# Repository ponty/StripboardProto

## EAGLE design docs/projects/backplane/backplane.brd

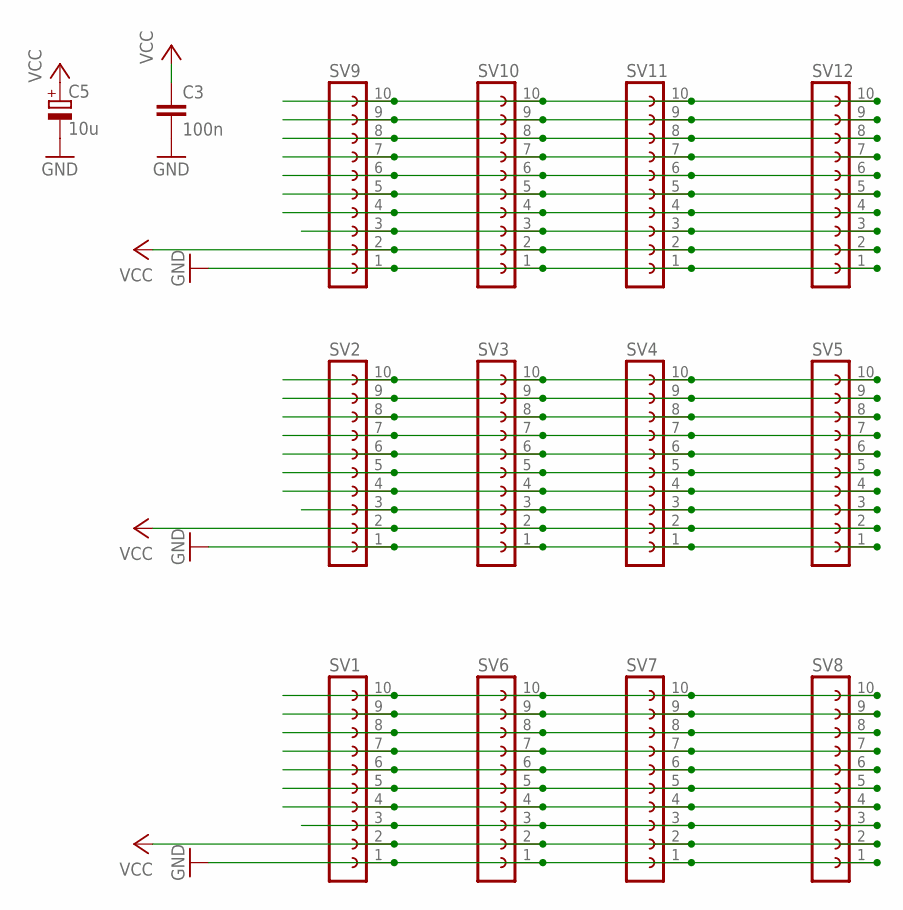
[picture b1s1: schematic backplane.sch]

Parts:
C3: 100n; C025-024X044
C5: 10u; E2,5-6E
SV1, SV2, SV3, SV4, SV5, SV6, SV7, SV8, SV9, SV10, SV11, SV12: FE10-1; FE10

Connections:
GND: C3.2, C5.-, SV1.1, SV2.1, SV3.1, SV4.1, SV5.1, SV6.1, SV7.1, SV8.1, SV9.1, SV10.1, SV11.1, SV12.1
unnamed: SV2.4, SV3.4, SV4.4, SV5.4
unnamed: SV2.10, SV3.10, SV4.10, SV5.10
unnamed: SV2.3, SV3.3, SV4.3, SV5.3
unnamed: SV2.9, SV3.9, SV4.9, SV5.9
unnamed: SV2.8, SV3.8, SV4.8, SV5.8
unnamed: SV2.7, SV3.7, SV4.7, SV5.7
unnamed: SV2.6, SV3.6, SV4.6, SV5.6
unnamed: SV2.5, SV3.5, SV4.5, SV5.5
unnamed: SV1.10, SV6.10, SV7.10, SV8.10
unnamed: SV1.9, SV6.9, SV7.9, SV8.9
unnamed: SV1.8, SV6.8, SV7.8, SV8.8
unnamed: SV1.7, SV6.7, SV7.7, SV8.7
unnamed: SV1.6, SV6.6, SV7.6, SV8.6
unnamed: SV1.5, SV6.5, SV7.5, SV8.5
unnamed: SV1.4, SV6.4, SV7.4, SV8.4
unnamed: SV1.3, SV6.3, SV7.3, SV8.3
unnamed: SV9.10, SV10.10, SV11.10, SV12.10
unnamed: SV9.9, SV10.9, SV11.9, SV12.9
unnamed: SV9.8, SV10.8, SV11.8, SV12.8
unnamed: SV9.7, SV10.7, SV11.7, SV12.7
unnamed: SV9.6, SV10.6, SV11.6, SV12.6
unnamed: SV9.5, SV10.5, SV11.5, SV12.5
unnamed: SV9.4, SV10.4, SV11.4, SV12.4
unnamed: SV9.3, SV10.3, SV11.3, SV12.3
VCC: C3.1, C5.+, SV1.2, SV2.2, SV3.2, SV4.2, SV5.2, SV6.2, SV7.2, SV8.2, SV9.2, SV10.2, SV11.2, SV12.2

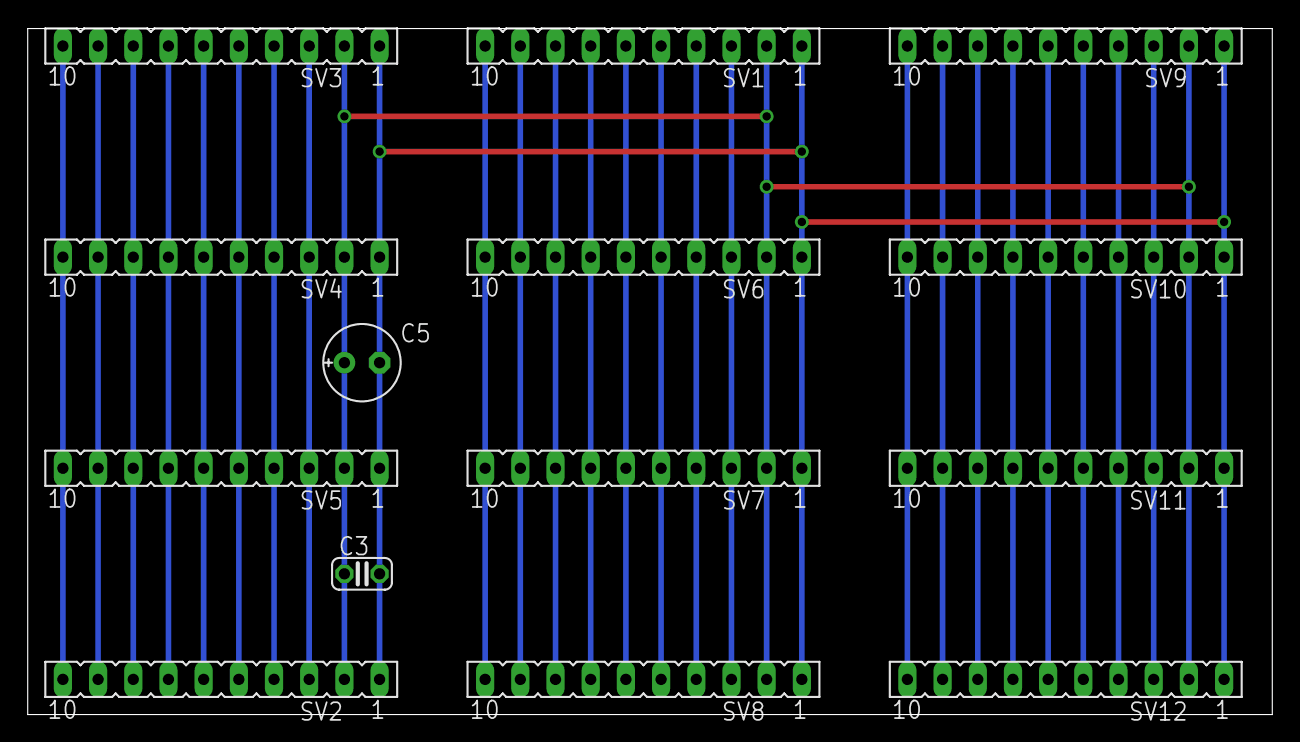
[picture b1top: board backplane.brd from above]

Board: 2 copper layers, 89.8 x 49.5 mm, 14 parts (0 on the bottom side), 26 nets.

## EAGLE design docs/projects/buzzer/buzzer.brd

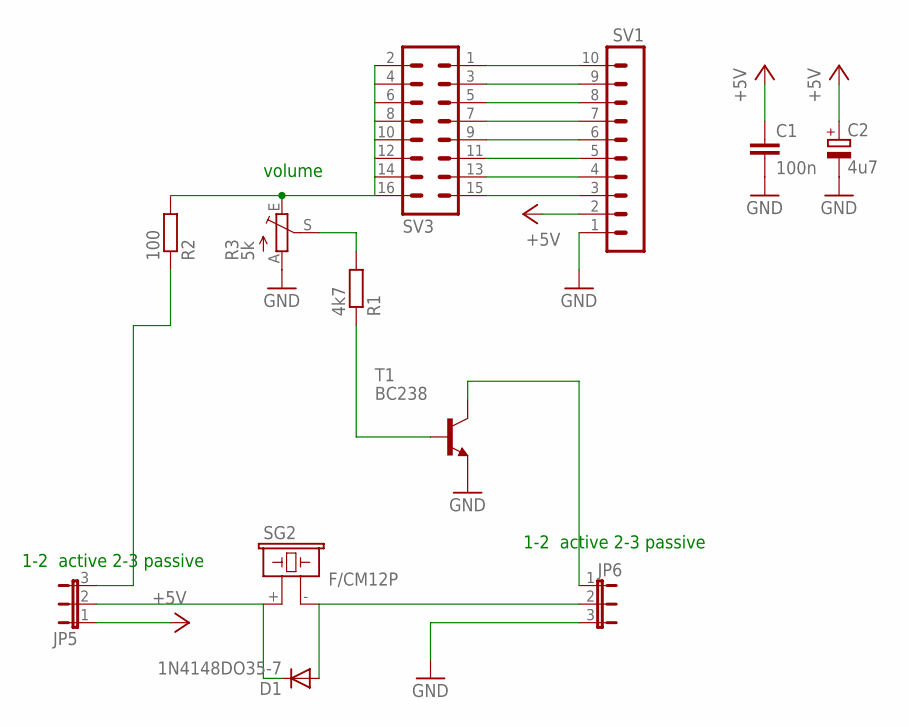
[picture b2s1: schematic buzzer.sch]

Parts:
C1: 100n; C025-024X044
C2: 4u7; TT2D5
D1: 1N4148DO35-7; DO35-7
JP5, JP6: JP2W
R1: 4k7; 0617/17
R2: 100; 0207/10
R3: 5k; CA9V
SG2: F/CM12P
SV1: MA10-1W
SV3: MA08-2
T1: BC238; TO5

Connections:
+5V: C1.1, C2.+, JP5.1, SV1.2
GND: C1.2, C2.-, JP6.3, R3.A, SV1.1, T1.1 (E)
unnamed: R2.2, R3.E, SV3.2, SV3.4, SV3.6, SV3.8, SV3.10, SV3.12, SV3.14, SV3.16
unnamed: R1.2, R3.S
unnamed: R1.1, T1.2 (B)
unnamed: D1.C, JP5.2, SG2.+ (1)
unnamed: JP5.3, R2.1
unnamed: SV1.3, SV3.15
unnamed: D1.A, JP6.2, SG2.- (2)
unnamed: SV1.4, SV3.13
unnamed: SV1.5, SV3.11
unnamed: JP6.1, T1.3 (C)
unnamed: SV1.6, SV3.9
unnamed: SV1.7, SV3.7
unnamed: SV1.8, SV3.5
unnamed: SV1.9, SV3.3
unnamed: SV1.10, SV3.1

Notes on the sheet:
1-2 active 2-3 passive
volume

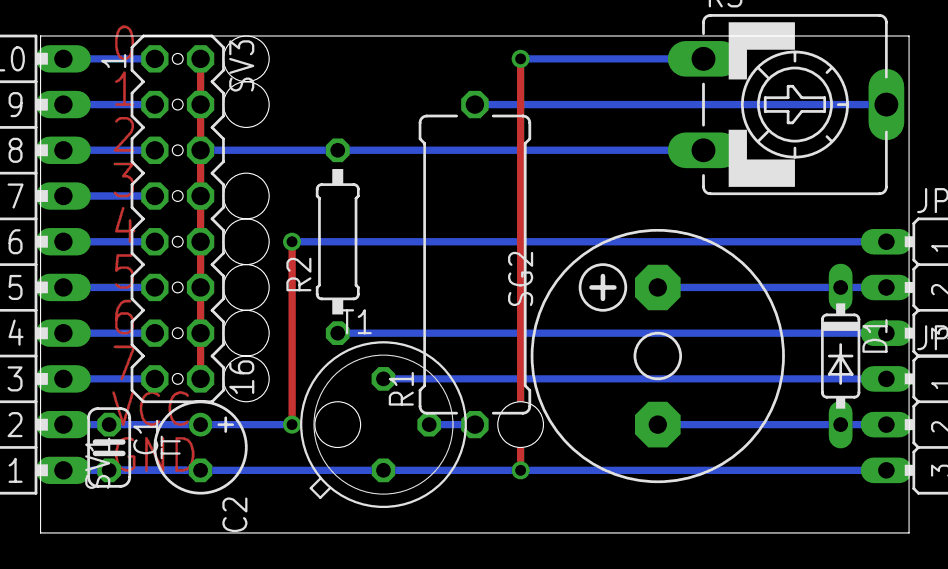
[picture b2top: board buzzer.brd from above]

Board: 2 copper layers, 48.2 x 27.6 mm, 12 parts (0 on the bottom side), 17 nets.

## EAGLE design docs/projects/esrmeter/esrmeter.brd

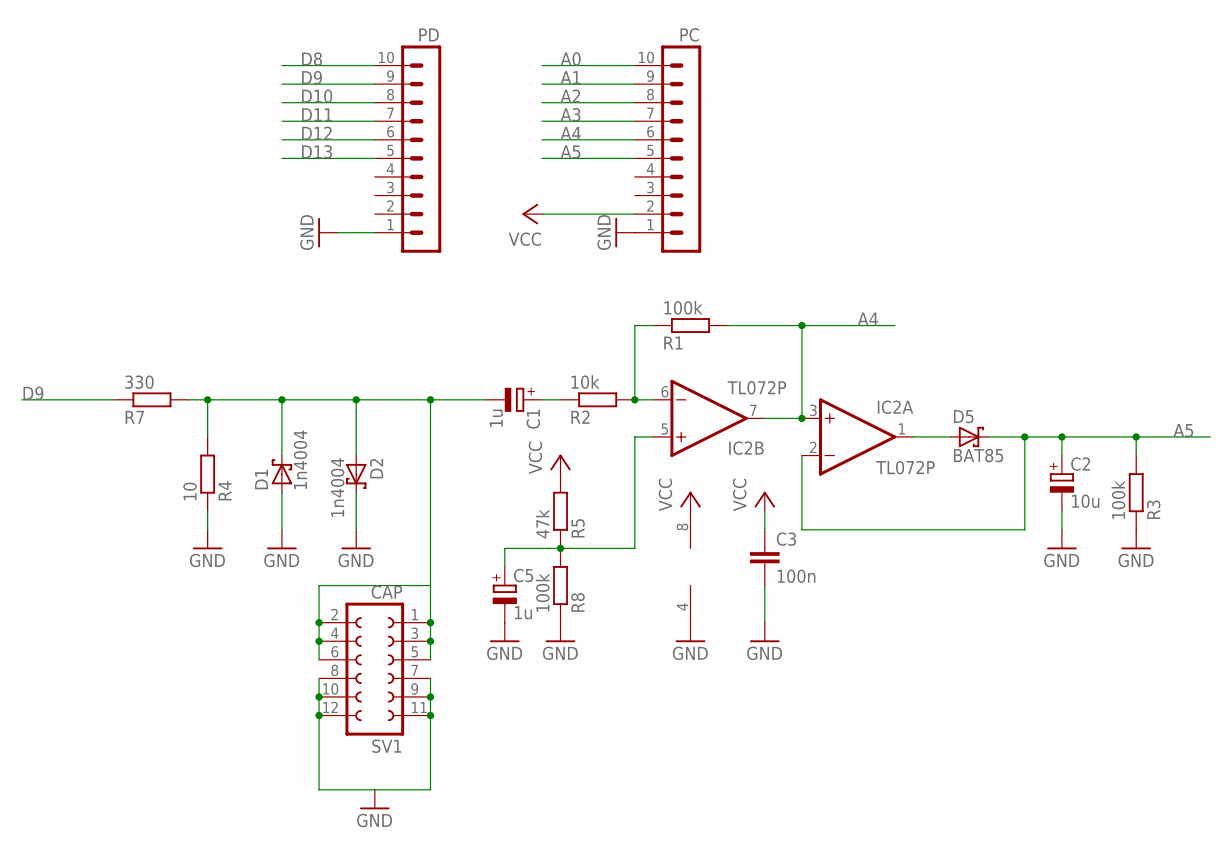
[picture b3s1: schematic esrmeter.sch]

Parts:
C1: 1u; TT2D6
C2: 10u; TT5D7
C3: 100n; C025-024X044
C5: 1u; TT5D7
D1, D2: 1n4004; TO92H
D5: BAT85; TO92H
IC2: TL072P; DIL08
PC: MA10-1W
PD: MA10-1W
R1: 100k; 0207/2V
R2: 10k; 0617/17
R3: 100k; 0207/10
R4: 10; 0207/2V
R5: 47k; 0207/2V
R7: 330; 0617/22
R8: 100k; 0204/5
SV1: CAP; FE06-2W

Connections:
A0: PC.10
A1: PC.9
A2: PC.8
A3: PC.7
A4: IC2.3 (+IN), IC2.7 (OUT), PC.6, R1.2
A5: C2.+, D5.2 (C), IC2.2 (-IN), PC.5, R3.2
D8: PD.10
D9: PD.9, R7.1
D10: PD.8
D11: PD.7
D12: PD.6
D13: PD.5
GND: C2.-, C3.2, C5.-, D1.1 (A), D2.2 (C), IC2.4 (V-), PC.1, PD.1, R3.1, R4.1, R8.1, SV1.7, SV1.8, SV1.9, SV1.10, SV1.11, SV1.12
unnamed: C1.-, D1.2 (C), D2.1 (A), R4.2, R7.2, SV1.1, SV1.2, SV1.3, SV1.4, SV1.5, SV1.6
unnamed: C1.+, R2.1
unnamed: IC2.6 (-IN), R1.1, R2.2
unnamed: D5.1 (A), IC2.1 (OUT)
unnamed: C5.+, IC2.5 (+IN), R5.1, R8.2
VCC: C3.1, IC2.8 (V+), PC.2, R5.2

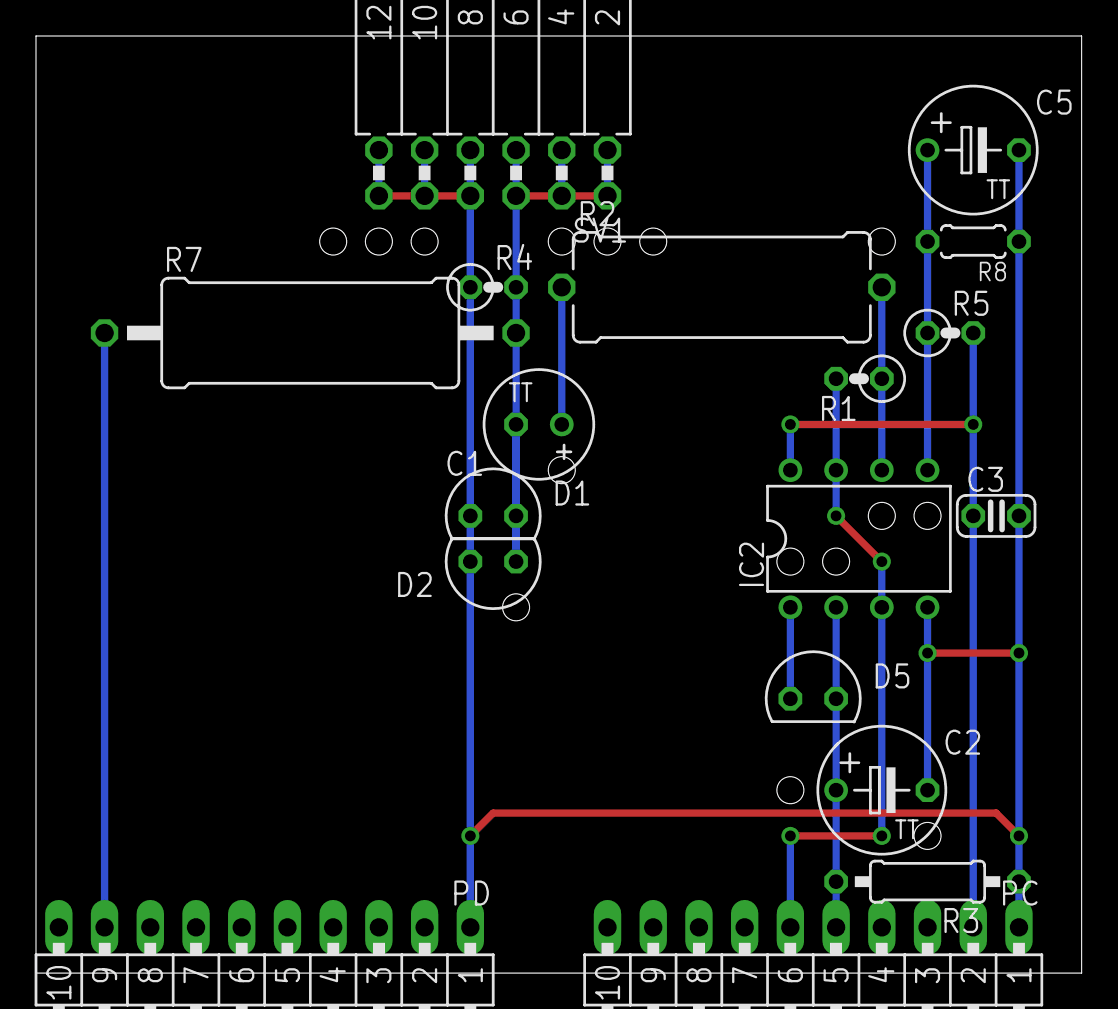
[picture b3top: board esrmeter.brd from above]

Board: 2 copper layers, 58.1 x 52.1 mm, 18 parts (0 on the bottom side), 10 nets.

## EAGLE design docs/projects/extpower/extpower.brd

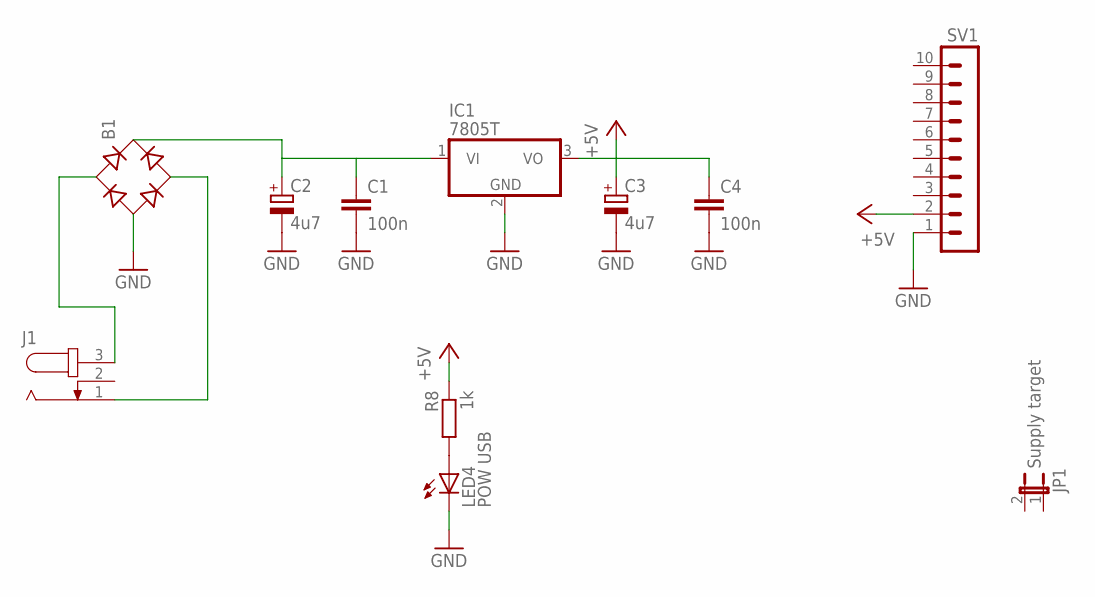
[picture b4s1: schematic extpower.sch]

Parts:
B1: RB1A
C1, C4: 100n; C025-024X044
C2, C3: 4u7; TT2D5
IC1: 7805T; TO220H
J1: JACK-PLUG0; SPC4077
JP1: Supply target; JP1
LED4: POW USB; LED3MM
R8: 1k; 0207/10
SV1: MA10-1W

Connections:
+5V: C3.+, C4.1, IC1.3 (VO), R8.1, SV1.2
GND: B1.-, C1.2, C2.-, C3.-, C4.2, IC1.2 (GND), LED4.K (C), SV1.1
unnamed: B1.AC1, J1.3
unnamed: B1.+, C1.1, C2.+, IC1.1 (VI)
unnamed: LED4.A, R8.2
unnamed: B1.AC2, J1.1

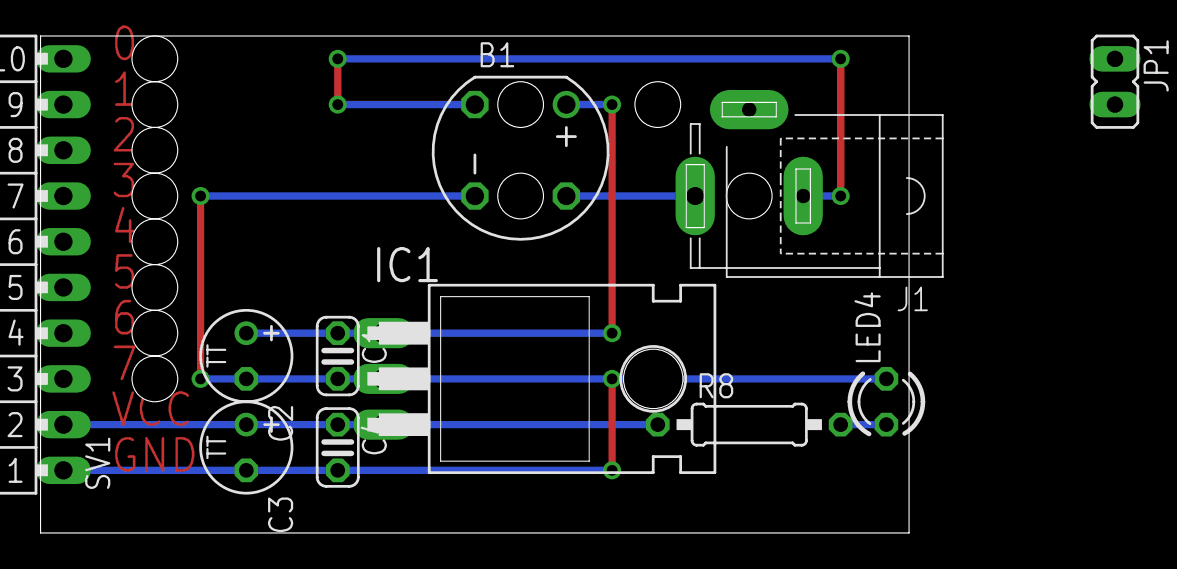
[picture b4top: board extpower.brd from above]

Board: 2 copper layers, 48.2 x 27.6 mm, 11 parts (0 on the bottom side), 6 nets.

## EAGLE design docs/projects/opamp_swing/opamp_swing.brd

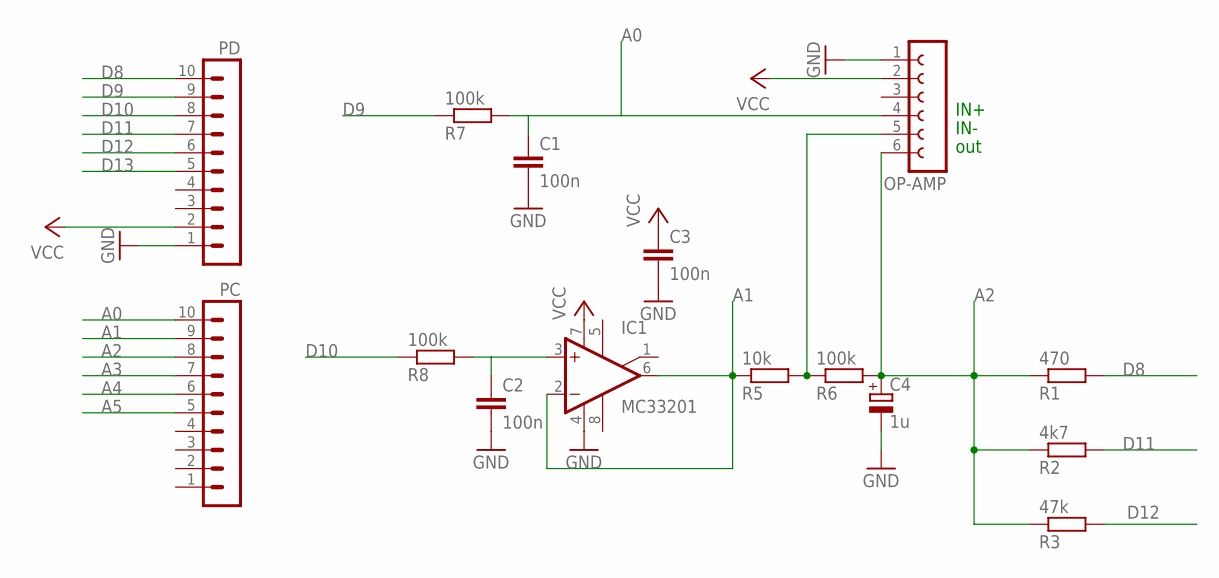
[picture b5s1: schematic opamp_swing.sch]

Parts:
C1: 100n; C050-025X075
C2, C3: 100n; C025-024X044
C4: 1u; 153CLV-0405
IC1: MC33201; DIL08
OP-AMP: FE06W
PC: MA10-1W
PD: MA10-1W
R1: 470; R1206
R2: 4k7; R1206
R3: 47k; R1206
R5: 10k; 0207/12
R6: 100k; 0207/2V
R7, R8: 100k; 0207/15

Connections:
A0: C1.1, OP-AMP.4, PC.10, R7.2
A1: IC1.2 (-IN), IC1.6 (OUT), PC.9, R5.1
A2: C4.+, OP-AMP.6, PC.8, R1.1, R2.1, R3.1, R6.2
A3: PC.7
A4: PC.6
A5: PC.5
D8: PD.10, R1.2
D9: PD.9, R7.1
D10: PD.8, R8.1
D11: PD.7, R2.2
D12: PD.6, R3.2
D13: PD.5
GND: C1.2, C2.2, C3.2, C4.-, IC1.4 (V-), OP-AMP.1, PD.1
unnamed: C2.1, IC1.3 (+IN), R8.2
unnamed: OP-AMP.5, R5.2, R6.1
VCC: C3.1, IC1.7 (V+), OP-AMP.2, PD.2

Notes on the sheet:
IN+
IN-
out

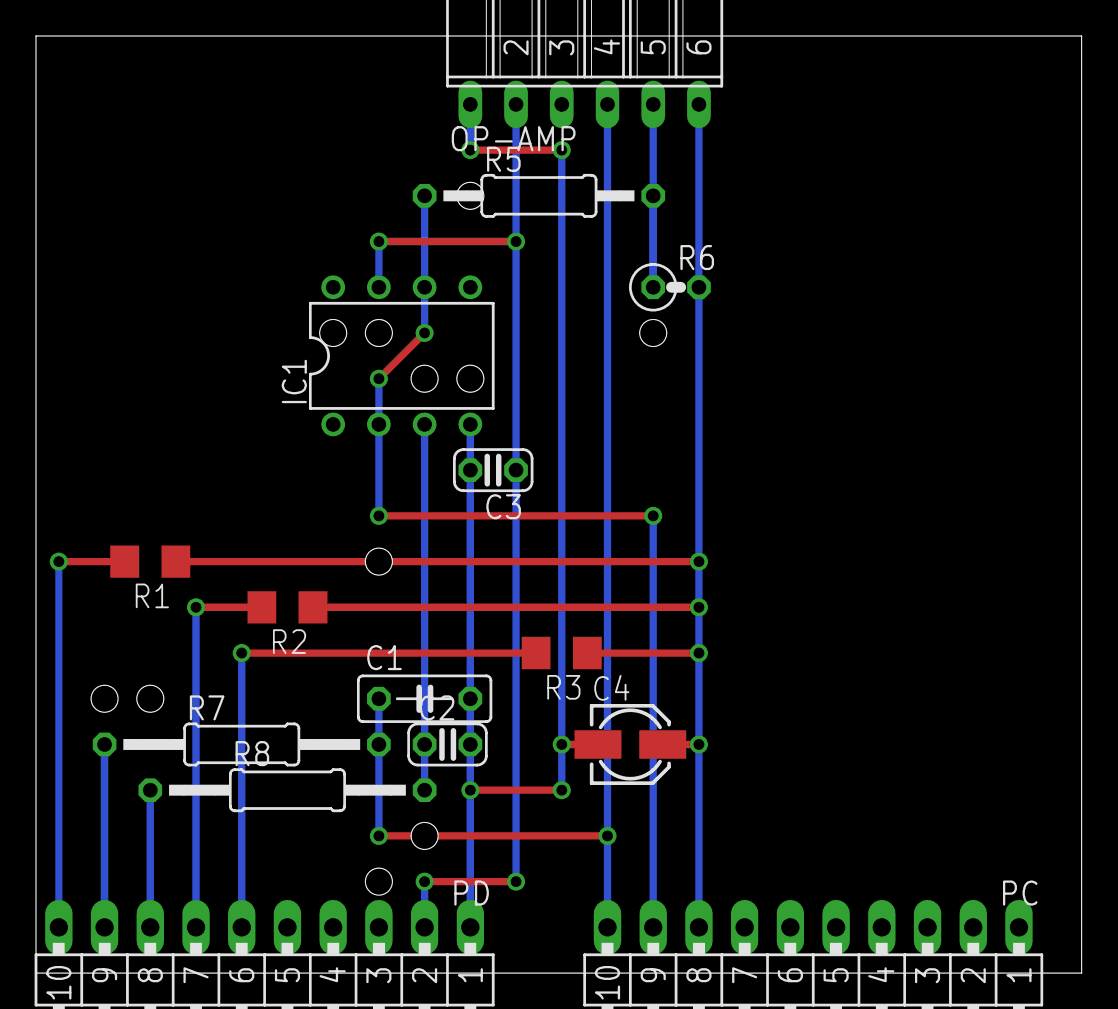
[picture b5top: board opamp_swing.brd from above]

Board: 2 copper layers, 58.1 x 52.1 mm, 15 parts (0 on the bottom side), 12 nets.

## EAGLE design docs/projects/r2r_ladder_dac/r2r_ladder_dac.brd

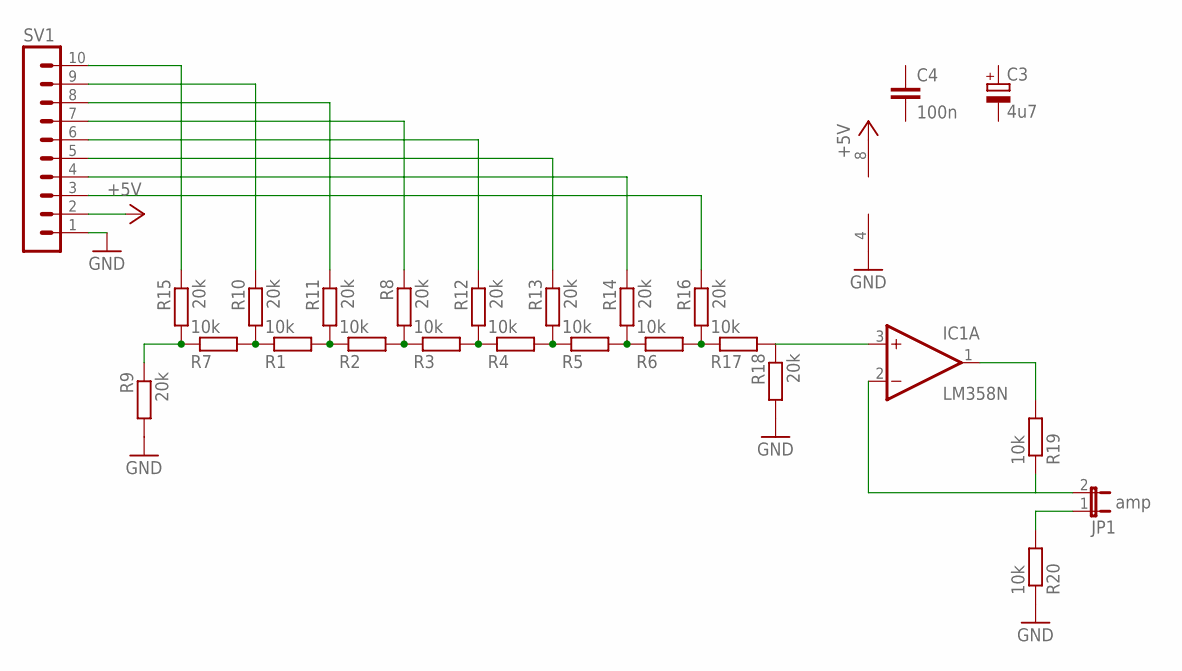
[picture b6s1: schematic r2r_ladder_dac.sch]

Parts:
C3: 4u7; TT2D5
C4: 100n; C025-024X044
IC1: LM358N; DIL08
JP1: amp; JP1
R1, R2, R3, R4, R5, R6, R7, R19, R20: 10k; 0204V
R8, R10, R11, R12, R13, R14, R15, R16, R18: 20k; 0207/10
R9: 20k; 0617/22
R17: 10k; 0204/5
SV1: MA10-1W

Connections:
+5V: IC1.8 (V+), SV1.2
GND: IC1.4 (V-), R9.2, R18.2, R20.1, SV1.1
unnamed: R1.2, R2.1, R11.2
unnamed: R2.2, R3.1, R8.2
unnamed: R3.2, R4.1, R12.2
unnamed: R7.1, R9.1, R15.2
unnamed: R4.2, R5.1, R13.2
unnamed: R5.2, R6.1, R14.2
unnamed: R1.1, R7.2, R10.2
unnamed: R6.2, R16.2, R17.1
unnamed: R15.1, SV1.10
unnamed: R10.1, SV1.9
unnamed: R11.1, SV1.8
unnamed: R8.1, SV1.7
unnamed: R12.1, SV1.6
unnamed: R13.1, SV1.5
unnamed: R14.1, SV1.4
unnamed: R16.1, SV1.3
unnamed: IC1.3 (+IN), R17.2, R18.1
unnamed: IC1.1 (OUT), R19.2
unnamed: IC1.2 (-IN), JP1.2, R19.1
unnamed: JP1.1, R20.2

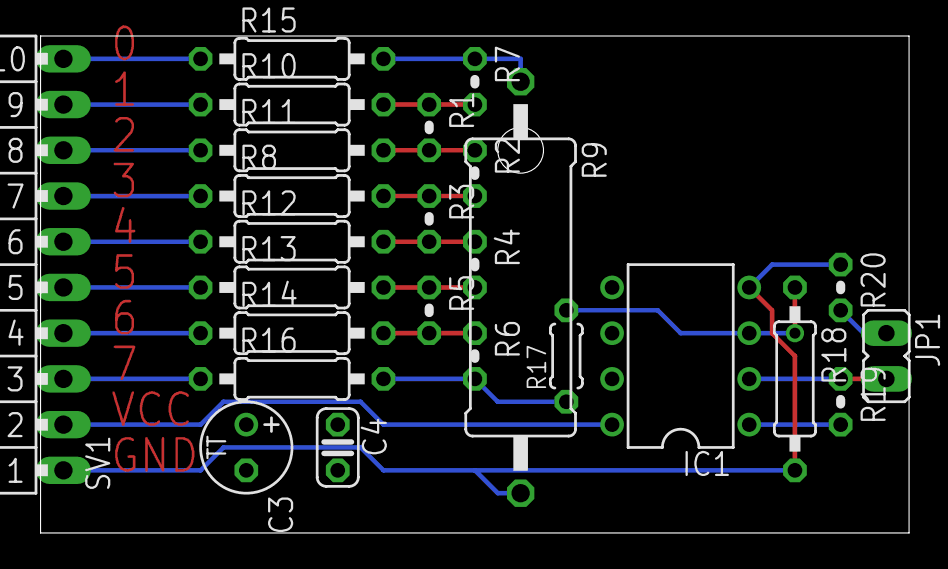
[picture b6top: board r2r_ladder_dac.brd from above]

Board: 2 copper layers, 48.2 x 27.6 mm, 25 parts (0 on the bottom side), 22 nets.

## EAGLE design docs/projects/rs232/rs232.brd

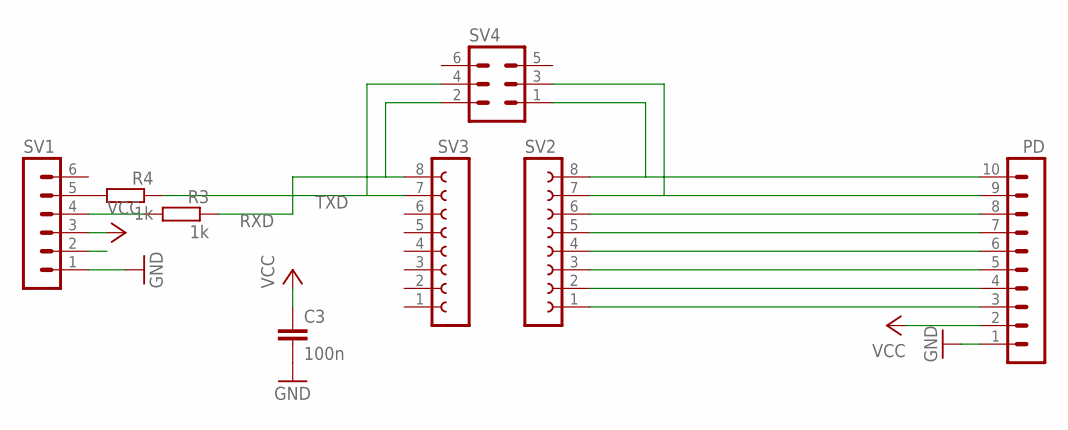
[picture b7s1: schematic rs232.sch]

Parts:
C3: 100n; C025-024X044
PD: MA10-1W
R3, R4: 1k; 0207/12
SV1: MA06-1
SV2, SV3: FE08-1; FE08
SV4: MA03-2

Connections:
GND: C3.2, PD.1, SV1.1
unnamed: PD.5, SV2.3
unnamed: PD.3, SV2.1
unnamed: PD.10, SV2.8, SV4.1
unnamed: PD.9, SV2.7, SV4.3
unnamed: R3.2, SV1.4
unnamed: R4.2, SV1.5
unnamed: PD.8, SV2.6
unnamed: PD.7, SV2.5
unnamed: PD.6, SV2.4
unnamed: PD.4, SV2.2
RXD: R3.1, SV3.8, SV4.2
TXD: R4.1, SV3.7, SV4.4
VCC: C3.1, PD.2, SV1.3

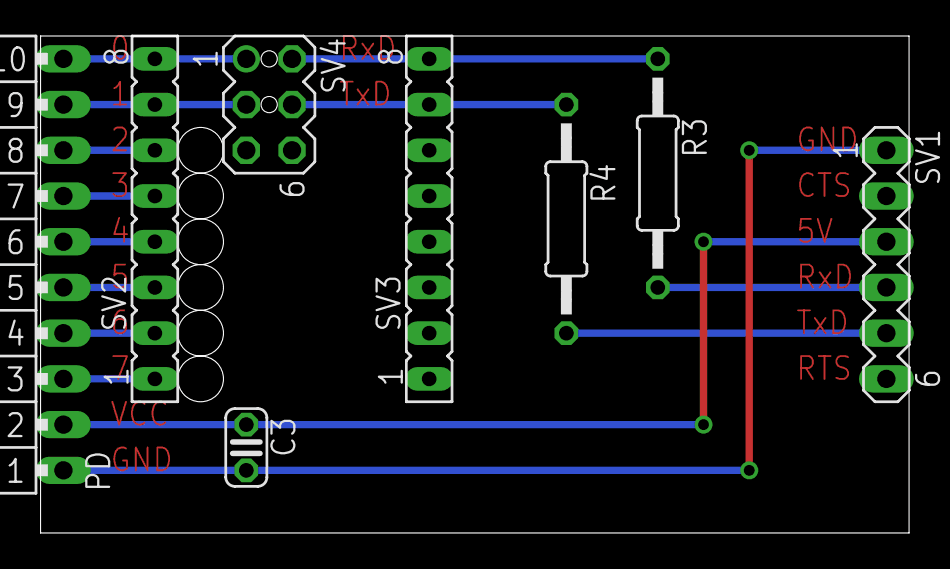
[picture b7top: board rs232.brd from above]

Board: 2 copper layers, 48.2 x 27.6 mm, 8 parts (0 on the bottom side), 14 nets.
